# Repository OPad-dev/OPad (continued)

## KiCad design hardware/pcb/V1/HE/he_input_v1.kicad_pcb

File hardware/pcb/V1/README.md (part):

# OPad V1 PCBs

Modular hardware ecosystem joined by one 8-wire JST-SH cable:

| Board | Folder | Size | Status | What it does |
|---|---|---|---|---|
| **Controller carrier** | `Carrier/` | 35.0 × 48.2 mm, C-shaped | Production | Plugs onto the Waveshare ESP32-S3-Touch-LCD-2 headers and brings the module signals to a connector |
| **MX input module** | `MX/` | 52.0 × 24.0 mm | Production | Two Kailh MX mechanical hot-swap sockets under the key plate |
| **Hall Effect input module** | `HE/` | 52.0 × 24.0 mm | **v2 Experimental** | Two magnetic Rapid Trigger Hall sensors (TI DRV5055) under the key plate |

> [!IMPORTANT]
> The **Hall Effect module** requires firmware v2 (Rapid Trigger support), which is not yet available. V1.1 is built and its sensors work on the bench (2026-10-19, [`docs/specs/v2-hall-effect-design.md`](../../docs/specs/v2-hall-effect-design.md) §10b); the firmware's ADC sampling pipeline and Rapid Trigger engine are specified in [`docs/specs/v2-rapid-trigger.md`](../../docs/specs/v2-rapid-trigger.md). v1 firmware recognises an HE module by its ID voltage, shows a warning on the LCD and ignores key input rather than reading the analog sensor outputs as presses.

The input module is **swappable**: both the MX mechanical module and the Hall-effect (rapid trigger) module use the same outline, mounting holes, connector position and pinout, and plug into the same carrier and cable. The module reports which kind it is through an ID voltage on the connector (0.30 V for MX, 1.06 V for Hall Effect).

Production files live in each board's `production/` folder, one subfolder per fab: `jlcpcb/` (Gerbers, BOM, CPL), `pcbway/` (Gerbers with their order marker, BOM, centroid) and `aisler/` (native KiCad board and ODB++ with the parts in them). Renders, PDFs, STEP and the ERC/DRC reports sit next to them.

Status: the MX module and the carrier pass ERC, DRC and schematic parity in KiCad 10.0.6 with zero errors; the carrier has zero warnings, the MX module only "does not match copy in library" warnings, because its footprint and symbol copies were placed before `lib/` was rewritten by `gen_library.py` (same pads and pins; that board is built and working, so `export_production.py` accepts them). The Hall Effect module is generated and checked by its own toolchain (`scripts/he_board.py`, see below), which needs no KiCad install; it reports zero rule violations, its Gerbers verify clean against the netlist, and the generated KiCad files pass ERC and DRC with schematic parity in KiCad 10.0.6 (`scripts/check_he_kicad.py`; only "footprint does not match library" warnings remain, see Toolchain).

---

## Module connector (JST SH 8-pin, same on every input module)

| Pin | Net | Waveshare pin | GPIO | MX V1 use | Hall module use |
|---|---|---|---|---|---|
| 1 | 3V3 | P2-1 | – | pull-ups, ID divider | sensor supply |
| 2 | GND | P2-2 | – | switch common | ground |
| 3 | IN1 | P1-10 | **GPIO10** (ADC1_CH9) | KEY1 (left key) | analog 1 / SPI CS1 |
| 4 | IN2 | P1-9 | **GPIO7** (ADC1_CH6) | KEY2 (right key) | analog 2 / SPI CS2 |
| 5 | ID | P1-8 | GPIO8 (ADC1_CH7) | ID divider = 0.30 V | own ID voltage |
| 6 | IO6 | P1-3 | GPIO6 (ADC1_CH5) | not used | e.g. SPI MISO |
| 7 | IO4 | P1-2 | GPIO4 (ADC1_CH3) | not used | e.g. SPI MOSI |
| 8 | IO2 | P1-1 | GPIO2 (ADC1_CH1) | not used | e.g. SPI SCK |

- All six signals are ADC1 pins. On the ESP32-S3, ADC continuous (DMA) mode only supports ADC1 (see `docs/specs/v2-rapid-trigger.md` §2.2).
- SPI3 can be routed to any of these pins through the GPIO matrix. None of them are strapping pins, USB, UART0, or the touch/IMU I2C.
- The pin order is chosen so both boards route on two layers with no crossings.
- **Firmware:** in the app, set Key 1 = GPIO10 and Key 2 = GPIO7 (both are already in the allowed pin list). The hand-wired defaults (GPIO14 / GPIO9) don't apply to this board.

### Module ID

Each module has its own divider from 3V3 to GND on ID. The carrier has no parts on this line.

| Module | Top resistor | Bottom resistor | ID voltage |
|---|---|---|---|
| MX V1 | 100 kΩ (R3) | 10 kΩ (R4) | 0.30 V |
| **Hall Effect V1** | **100 kΩ (R1)** | **47 kΩ (R2)** | **1.06 V** |
| reserved: Hall SPI | 100 kΩ | 100 kΩ | 1.65 V |

The divider's source impedance is 100k ∥ 47k ≈ 32 kΩ, above the ~10 kΩ the ESP32-S3 ADC likes. ID is read once at start-up, so average a handful of samples instead of trusting a single conversion.

With no module plugged in, GPIO8 floats. The firmware can enable the internal pull-down to read about 0 V in that case.

---

## MX input module (`MX/`)

- **Case coordinates** below are those of `hardware/3d/custom_case/V1/opad_enclosure.scad`: origin at the front-left outer corner, X to the right, Y toward the screen. KiCad uses X = 100 + case X and Y = 100 − case Y, so the top of the KiCad editor is the rear of the case and the layout is not mirrored.
- **Key centres:** case (28.475, 16.5) and (47.525, 16.5), 19.05 mm pitch, the same as the plate cutouts.
- **Outline:** case X 12…64, Y 7…31, 1.5 mm corner radius.
- **Mounting holes:** 2× M2 (2.2 mm NPTH) at case (15.5, 16.5) and (60.5, 16.5), on the key axis and clear of the switch footprints. The PCB must be held there, or it moves when a switch is pulled. Case V1.1 does this without screws: pins in the key deck go through the holes and posts on the bottom plate clamp the PCB against the deck.
- **Height:** the PCB top is **5.0 mm below the top of the plate** (plate 1.5 mm, case z = 10.0). About 3.5 mm of free space is needed under the PCB bottom for the sockets (1.85 mm) and J1 (2.9 mm).
- **Everything is on the bottom side** (sockets, J1, R1–R4, C1), so JLCPCB assembles one side only. The switches go in from the top through the plate.
- **J1** sits at the rear edge, centred on the keys, with the opening facing the screen. The cable leaves toward the controller.
- **Footprint:** `lib/opad.pretty/Kailh_CPG151101S11_MX_Hotswap_Bottom` is the Kailh land pattern (3.05 mm pin holes, 4.0 mm centre, 1.75 mm pegs, 2.55 × 2.5 mm pads), drawn from the socket side and placed flipped. The switch pins point to the rear (standard orientation).

## Hall Effect input module (`HE/`)

Same outline, mounting holes, connector position and pinout as the MX module, so the two are interchangeable on one cable. Instead of switching a pin to ground, each key has a **TI DRV5055A3 ratiometric linear Hall sensor** whose analog output tracks the magnet in the switch stem, which is what rapid trigger needs.

> **V1.0 erratum (fixed in V1.1):** the V1.0 SOT-23 footprint was mirrored, so every assembled sensor sits with **VCC on its IN line and OUT on 3V3**. It powers itself backwards through its protection diode, reads a fixed ~2.9 V and barely reacts to a magnet. The connectivity was right, so neither DRC nor the assembler could catch it. V1.1 swaps pads 1 and 2 (`scripts/gen_library.py`, `scripts/he_board.py`), moves C2/C3 to the pin-1 side so the 3V3 stub and the IN line do not cross, and `he_board.py`'s self-test now checks every SOT-23's pin order against the real package. A V1.0 board works only with each sensor re-soldered upside down (marking towards the board), which mirrors its pin order back.
>
> **V1.1 review (2026-10-10), before ordering:** TI's DBZ pinout (datasheet SBAS640C Figure 4-1 and Table 4-1: 1 = VCC, 2 = OUT, 3 = GND, pin 1 top-left in the top view) was checked against the footprint by hand, against KiCad's flip convention and against the V1.0 measurements; the three agree with the V1.1 pads. Found and fixed in the same pass: the vias grow from 0.6 to **0.7 mm** (0.2 mm annular ring, which Aisler's HASL rules and Eurocircuits' class 6 need; JLCPCB accepted 0.6); the silkscreen square round each sensor was 3.0 mm and crossed the pad tips, it is now 3.6 mm with a pin-1 dot, and `C2`/`C3` moved 0.2 mm away from the sensors to make room; the pour gap went from 0.3 to 0.45 mm and a ground via fills the pocket next to U2, so the Gerbers hold no floating copper slivers (`verify_he_gerbers.py` now checks for islands); the generated schematic had an unescaped quote and did not load in KiCad, so ERC had never actually run on it (it now passes, with PWR_FLAGs and a connector symbol that carries the MP pads). None of these change the netlist.

### Sensor architecture (the part that matters)

This is **Architecture A: bottom-side SMT on solid FR-4.**

- There is **no 4.0 mm stem hole** at the key centres. `SW_MX_Hall_PlateMount` (used for a through-hole stem) is *not* the footprint here; `SW_MX_Hall_PlateMount_SolidCentre` is, and it contributes only the two alignment peg holes.
- U1 and U2 are centred **exactly** on the key centres (16.475, 9.5) and (35.525, 9.5), on the bottom copper, directly under the magnet.
- A **3.0 × 3.0 mm copper keepout on both layers** around each sensor keeps the ground pour out of the magnetic path, so the stem magnet's flux is not damped by eddy currents in the plane. In KiCad these are rule areas with `copperpour not_allowed`; in the Gerbers the pour is genuinely absent there.
### Why there is no centre hole, and what the board is actually compatible with

In a Lekker / Gateron KS-20 class magnetic switch (Gateron's KS-20T drawing DS-02-001-A0, in the [Magnetic Orange datasheet](https://gateron.com/u_file/2312/26/file/GATERONMagneticOrangeSwitch-KS-20TO10B050NW-Y64.pdf), sheet 1):

- **the magnet sits in the stem at the switch centre, N pole towards the PCB.** There is no MX-style centre pole and no 4 mm centre hole;
- **two Ø 1.70 ± 0.05 mm plastic pins, 10.16 mm apart (±5.08 mm), stick out of the bottom and pass straight through the PCB**, protruding about 1 mm out the back. That is why the 1.75 mm peg holes are needed;
- the bottom housing has a pocket ("the hole for setting hall sensor") so Gateron's own reference layout puts a SOT-23 sensor on the **top** of the PCB, between the two pins, with three 0.8 × 0.8 mm pads.

So a top-side sensor is possible with these switches; this board puts it on the bottom instead, like Wooting ([Lekker update #5, part 2](https://wooting.io/post/we-overcame-the-challenges-lekker-update-5-part-22)), because single-side assembly is cheaper and the top of the PCB stays flat against the plate. The price is distance: the magnet reads through the full 1.6 mm of FR-4 plus the package, so the field at the die is a fraction of what Gateron's pocket position sees (numbers under Sensor sensitivity). Peg holes **and** a solid centre **and** a bottom-side sensor is a consistent set; a board that had the peg holes *and* a 4 mm centre hole would be an MX PCB-mount pattern, which is a different switch.

| Switch | Works on this board? |
|---|---|
| Gateron KS-20 / Wooting Lekker, KS-37 / Magnetic Jade, Geon Raw HE and other Lekker-standard magnetic switches | Yes — flush magnet centre, two ±5.08 mm plastic pins |
| Switches sold as "**TMR switches**" | Yes — see below |
| MX mechanical (Cherry, Gateron, Kailh…) | **No.** A real MX switch has a centre pole and metal pins. That is what the `MX/` module is for — same outline, same connector, swap the module |

**On "TMR switches":** TMR (tunnel magnetoresistance) is a *sensor* technology that lives on the keyboard's PCB, not a different kind of switch. A switch marketed as a "TMR switch" is the same magnetic switch — a magnet in an MX-form stem with a flush bottom and two pins — and the industry uses them interchangeably: Gateron Jade, Jade Pro and Lekker V2 all go into Hall boards like the Wooting 60HE and TMR boards like the Womier SK75 alike. This module reads the magnet with a Hall sensor, and the magnet does not know or care what sensor is underneath it, so TMR-branded switches drop straight in.

Two caveats, neither of which is a fit problem:

- **Magnet strength varies by switch model.** TMR sensors are far more sensitive than Hall, so a vendor *can* pair a TMR-targeted switch line with a weaker magnet. If you use such a switch here, A3 is the wrong variant and you want A1 or A2. As Wooting put it, what matters is matching the sensitivity range to the magnet, not chasing sensitivity for its own sake.
- **This board cannot be rebuilt with a TMR sensor as a drop-in.** The common analog TMR parts (MultiDimension TMR2001, TMR2083) are SOT-23-**5**, not the 3-pin SOT-23 used here, so they would need a new footprint and a re-route. Most TMR designs also mount the sensor *off-axis*; U1/U2 here are deliberately on-axis at the key centre, which is the right placement for the DRV5055.

These magnetic switches are deliberately not MX-compatible; vendors say so themselves. The claim this board makes is "every switch in the Lekker standard", not "every keyboard switch ever made". If a magnetic switch turns up with a protruding MX-style centre pole, it will foul the sensor and is out of scope for V1 — I found no current HE switch that does this, since the whole class puts the magnet where that pole would be.

### Sensor sensitivity

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
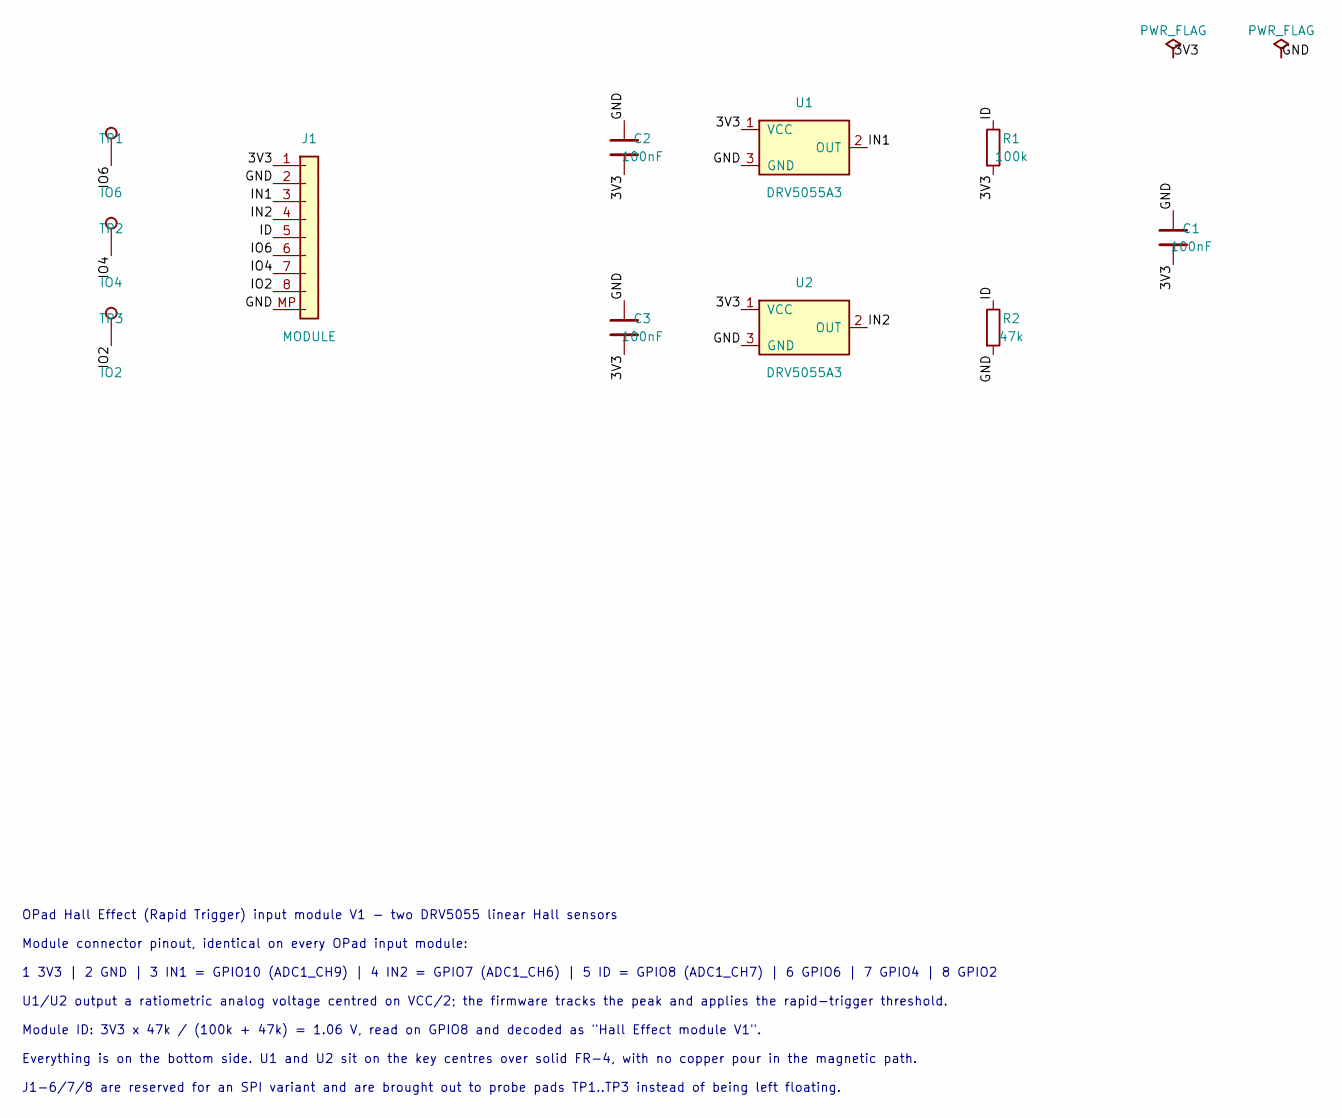
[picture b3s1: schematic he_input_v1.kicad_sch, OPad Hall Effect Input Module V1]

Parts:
C1, C2, C3: 100nF; C_0603_1608Metric; MPN CC0603KRX7R9BB104; LCSC C14663
J1: MODULE; JST_SH_SM08B-SRSS-TB_1x08-1MP_P1.00mm_Horizontal; MPN SM08B-SRSS-TB(LF)(SN); LCSC C160407
R1: 100k; R_0603_1608Metric; MPN 0603WAF1003T5E; LCSC C25803
R2: 47k; R_0603_1608Metric; MPN 0603WAF4702T5E; LCSC C25819
TP1: IO6; TestPoint_Pad_1.0x1.0mm
TP2: IO4; TestPoint_Pad_1.0x1.0mm
TP3: IO2; TestPoint_Pad_1.0x1.0mm
U1, U2: DRV5055A3; SOT-23; MPN DRV5055A3QDBZR; LCSC C266128

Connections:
/3V3: C1.2, C2.2, C3.2, J1.1, R1.2, U1.1 (VCC), U2.1 (VCC)
/GND: C1.1, C2.1, C3.1, J1.2, J1.MP, R2.2, U1.3 (GND), U2.3 (GND)
/ID: J1.5, R1.1, R2.1
/IN1: J1.3, U1.2 (OUT)
/IN2: J1.4, U2.2 (OUT)
/IO2: J1.8, TP3.1
/IO4: J1.7, TP2.1
/IO6: J1.6, TP1.1

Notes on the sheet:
OPad Hall Effect (Rapid Trigger) input module V1 - two DRV5055 linear Hall sensors
Module connector pinout, identical on every OPad input module:
1 3V3 | 2 GND | 3 IN1 = GPIO10 (ADC1_CH9) | 4 IN2 = GPIO7 (ADC1_CH6) | 5 ID = GPIO8 (ADC1_CH7) | 6 GPIO6 | 7 GPIO4 | 8 GPIO2
U1/U2 output a ratiometric analog voltage centred on VCC/2; the firmware tracks the peak and applies the rapid-trigger threshold.
Module ID: 3V3 x 47k / (100k + 47k) = 1.06 V, read on GPIO8 and decoded as "Hall Effect module V1".
Everything is on the bottom side. U1 and U2 sit on the key centres over solid FR-4, with no copper pour in the magnetic path.
J1-6/7/8 are reserved for an SPI variant and are brought out to probe pads TP1..TP3 instead of being left floating.

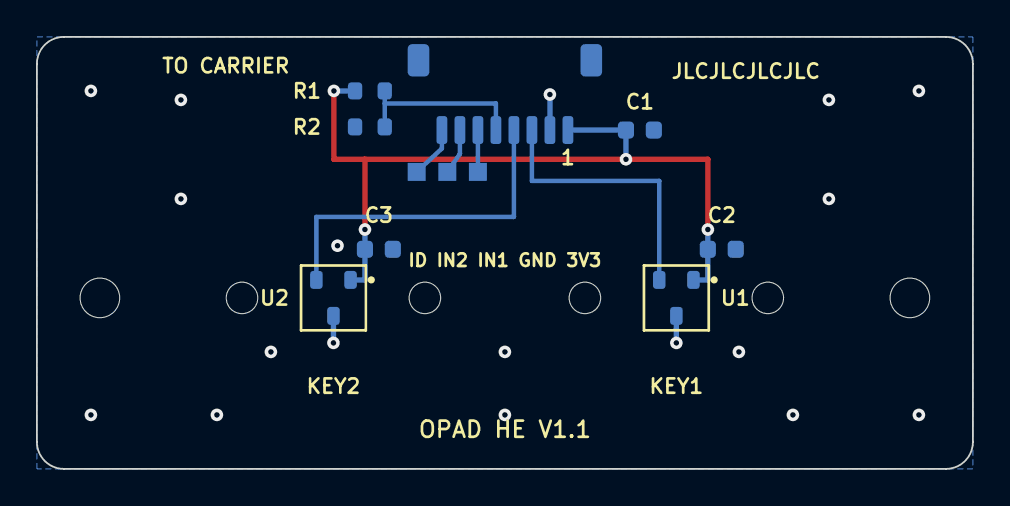
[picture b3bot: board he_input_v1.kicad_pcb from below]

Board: 2 copper layers, 52.0 x 24.0 mm, 15 parts (13 on the bottom side), 8 nets.

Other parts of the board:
H1, H2: MountingHole_2.2mm_M2
SW1: KEY1; SW_MX_Hall_PlateMount_SolidCentre
SW2: KEY2; SW_MX_Hall_PlateMount_SolidCentre

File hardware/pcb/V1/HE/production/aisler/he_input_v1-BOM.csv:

Reference,Quantity,Value,Footprint,MFG,MPN,LCSC,Side,Type
"U1,U2",2,DRV5055A3,SOT-23,Texas Instruments,DRV5055A3QDBZR,C266128,bottom,SMD
"C2,C3,C1",3,100nF,C_0603_1608Metric,YAGEO,CC0603KRX7R9BB104,C14663,bottom,SMD
"J1",1,MODULE,JST_SH_SM08B-SRSS-TB_1x08-1MP_P1.00mm_Horizontal,JST,SM08B-SRSS-TB(LF)(SN),C160407,bottom,SMD
"R1",1,100k,R_0603_1608Metric,UNI-ROYAL,0603WAF1003T5E,C25803,bottom,SMD
"R2",1,47k,R_0603_1608Metric,UNI-ROYAL,0603WAF4702T5E,C25819,bottom,SMD

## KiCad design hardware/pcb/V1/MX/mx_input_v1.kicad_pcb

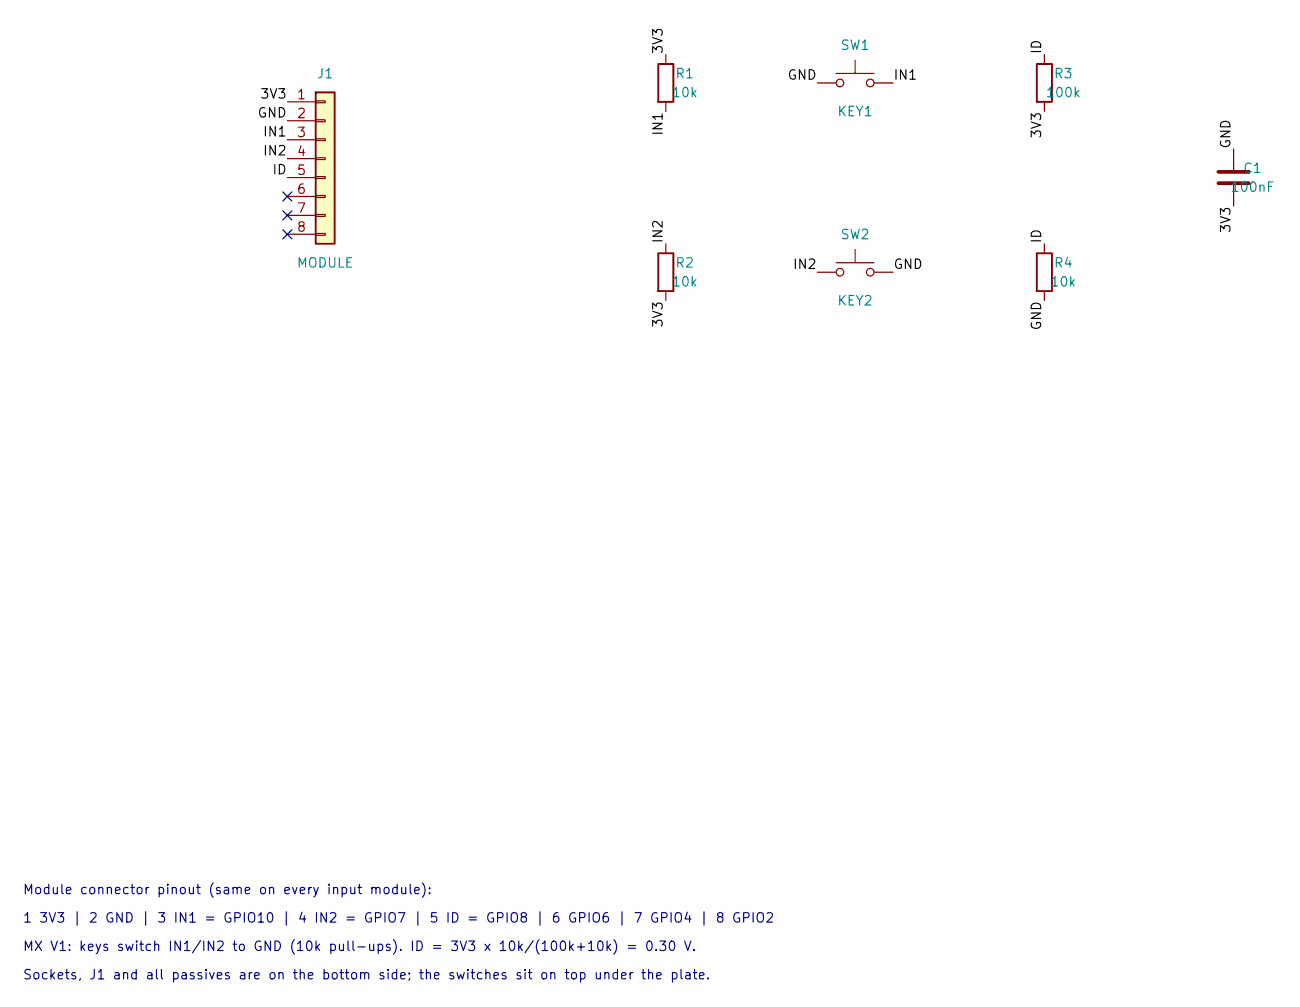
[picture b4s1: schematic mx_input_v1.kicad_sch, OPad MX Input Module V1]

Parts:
C1: 100nF; C_0603_1608Metric; MPN YAGEO CC0603KRX7R9BB104; LCSC C14663
J1: MODULE; JST_SH_SM08B-SRSS-TB_1x08-1MP_P1.00mm_Horizontal; MPN JST SM08B-SRSS-TB(LF)(SN); LCSC C160407
R1, R2, R4: 10k; R_0603_1608Metric; MPN UNI-ROYAL 0603WAF1002T5E; LCSC C25804
R3: 100k; R_0603_1608Metric; MPN UNI-ROYAL 0603WAF1003T5E; LCSC C25803
SW1: KEY1; Kailh_CPG151101S11_MX_Hotswap_Bottom; MPN Kailh CPG151101S11; LCSC C41430893
SW2: KEY2; Kailh_CPG151101S11_MX_Hotswap_Bottom; MPN Kailh CPG151101S11; LCSC C41430893

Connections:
/3V3: C1.2, J1.1, R1.1, R2.2, R3.2
/GND: C1.1, J1.2, R4.2, SW1.1, SW2.2
/ID: J1.5, R3.1, R4.1
/IN1: J1.3, R1.2, SW1.2
/IN2: J1.4, R2.1, SW2.1

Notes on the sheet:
Module connector pinout (same on every input module):
1 3V3 | 2 GND | 3 IN1 = GPIO10 | 4 IN2 = GPIO7 | 5 ID = GPIO8 | 6 GPIO6 | 7 GPIO4 | 8 GPIO2
MX V1: keys switch IN1/IN2 to GND (10k pull-ups). ID = 3V3 x 10k/(100k+10k) = 0.30 V.
Sockets, J1 and all passives are on the bottom side; the switches sit on top under the plate.

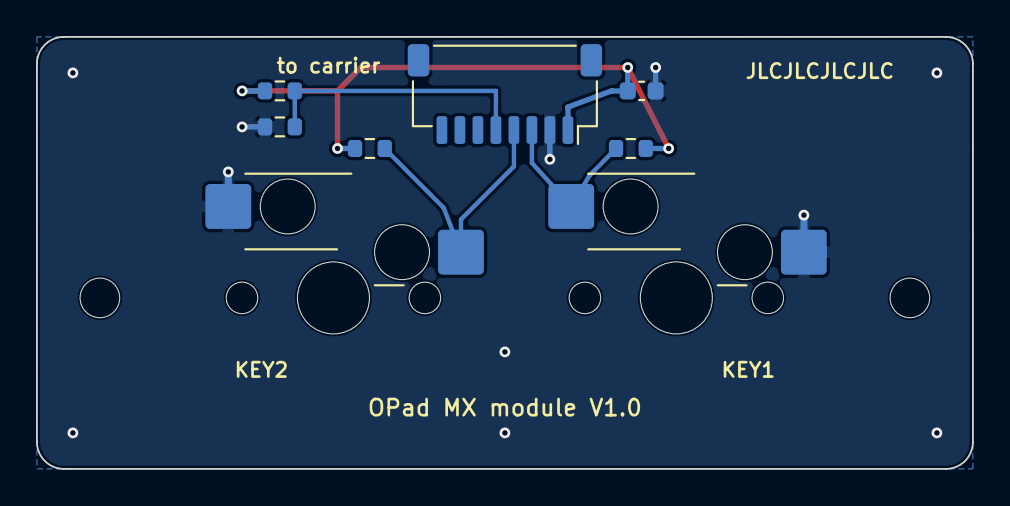
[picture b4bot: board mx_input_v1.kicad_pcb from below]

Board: 2 copper layers, 52.0 x 24.0 mm, 10 parts (8 on the bottom side), 5 nets.

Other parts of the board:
H1, H2: MountingHole_2.2mm_M2

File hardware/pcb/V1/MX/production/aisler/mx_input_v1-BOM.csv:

Reference,Quantity,Value,Footprint,MFG,MPN,LCSC,Side,Type
"R1,R2,R4",3,10k,R_0603_1608Metric,UNI-ROYAL,0603WAF1002T5E,C25804,bottom,SMD
"C1",1,100nF,C_0603_1608Metric,YAGEO,CC0603KRX7R9BB104,C14663,bottom,SMD
"J1",1,MODULE,JST_SH_SM08B-SRSS-TB_1x08-1MP_P1.00mm_Horizontal,JST,SM08B-SRSS-TB(LF)(SN),C160407,bottom,SMD
"R3",1,100k,R_0603_1608Metric,UNI-ROYAL,0603WAF1003T5E,C25803,bottom,SMD
"SW2",1,KEY2,Kailh_CPG151101S11_MX_Hotswap_Bottom,Kailh,CPG151101S11,C41430893,bottom,SMD
"SW1",1,KEY1,Kailh_CPG151101S11_MX_Hotswap_Bottom,Kailh,CPG151101S11,C41430893,bottom,SMD

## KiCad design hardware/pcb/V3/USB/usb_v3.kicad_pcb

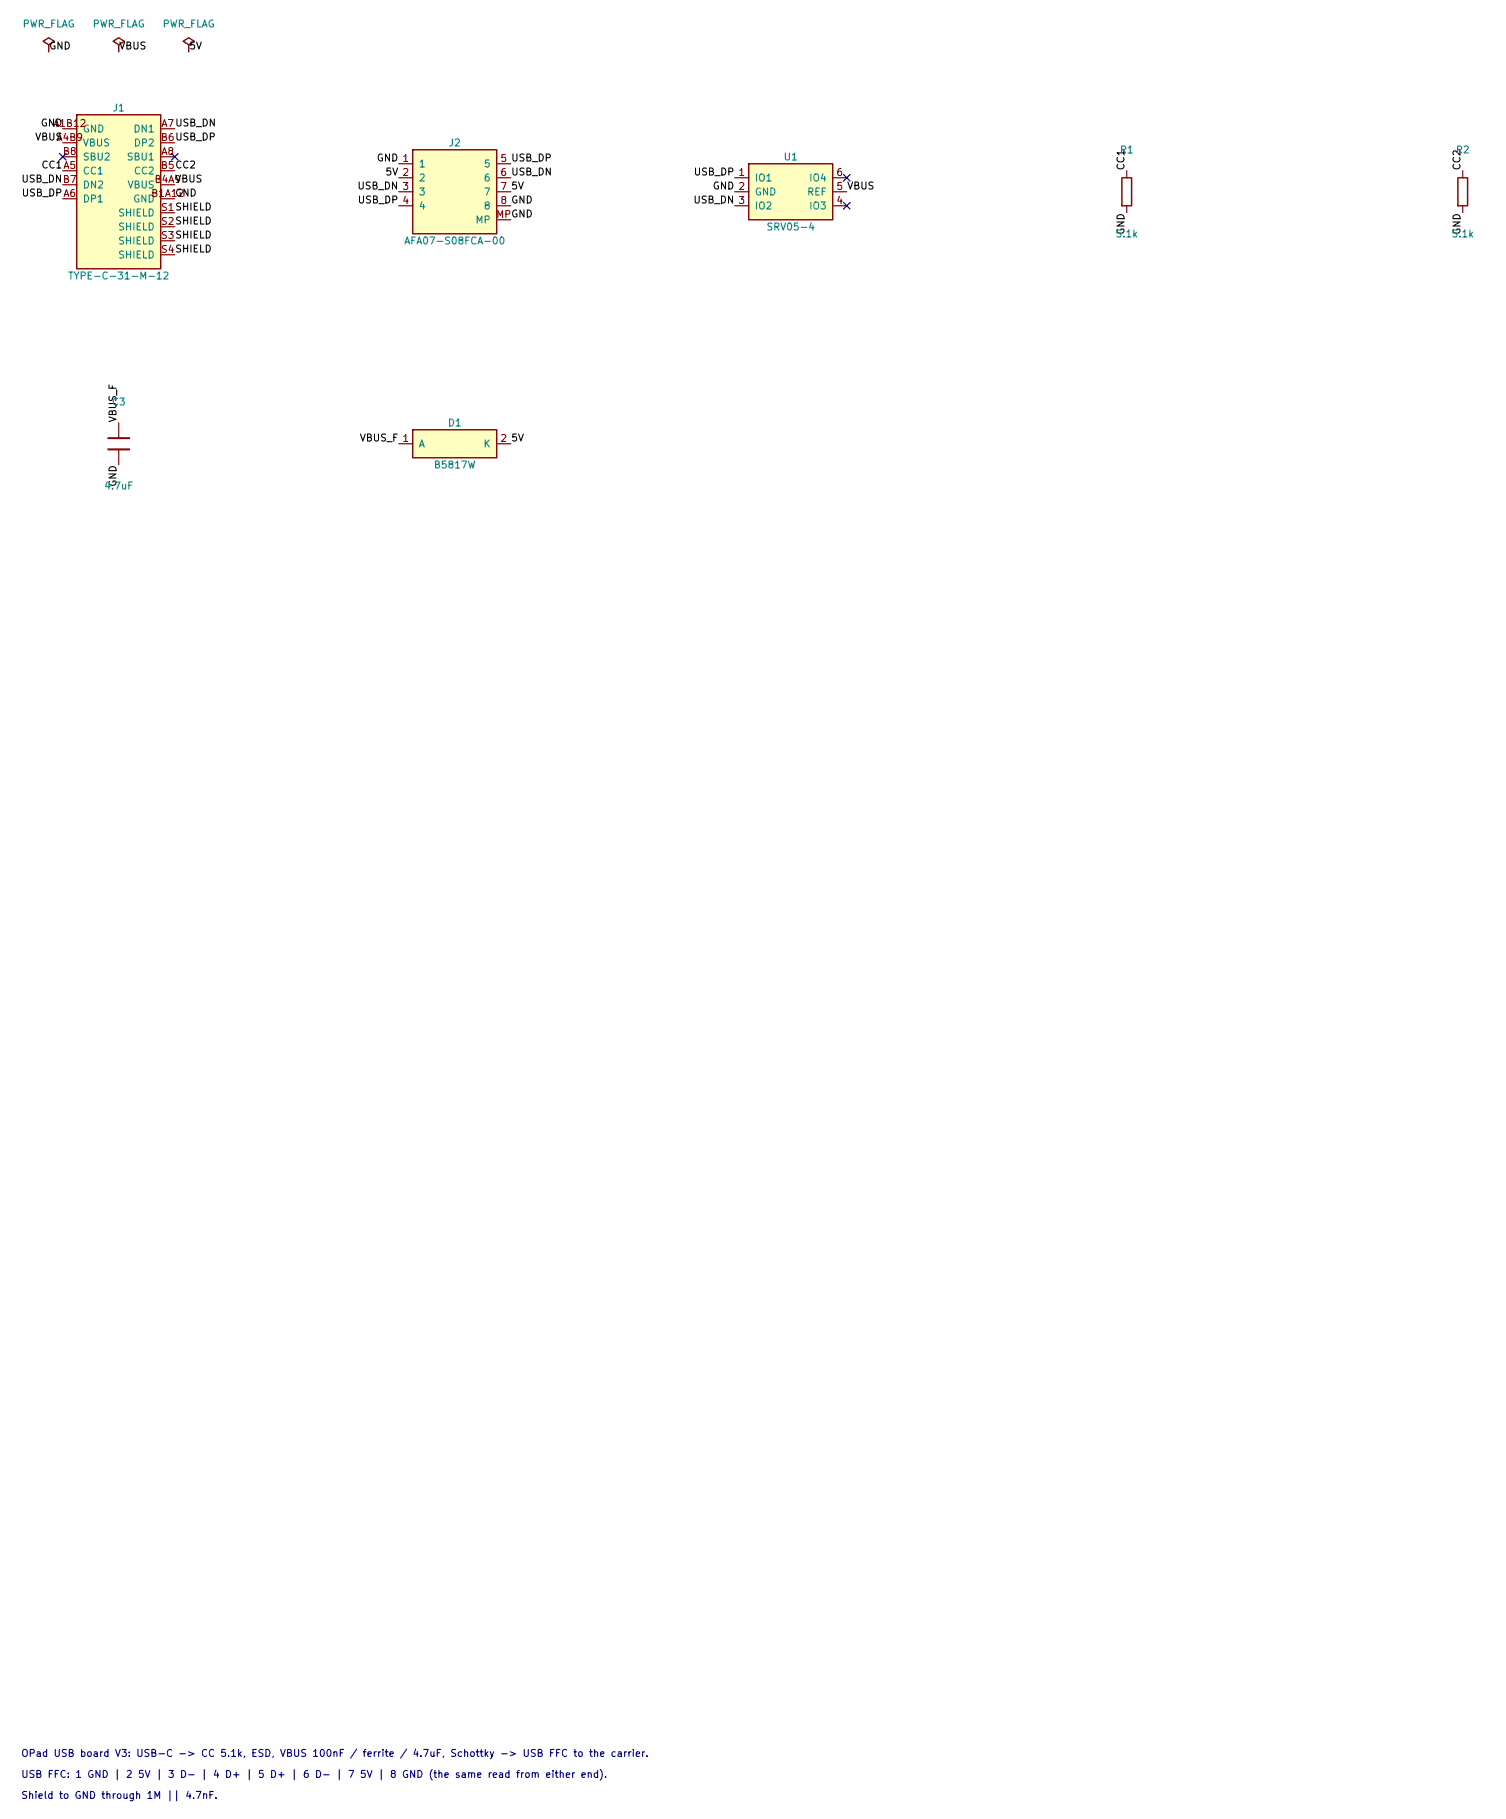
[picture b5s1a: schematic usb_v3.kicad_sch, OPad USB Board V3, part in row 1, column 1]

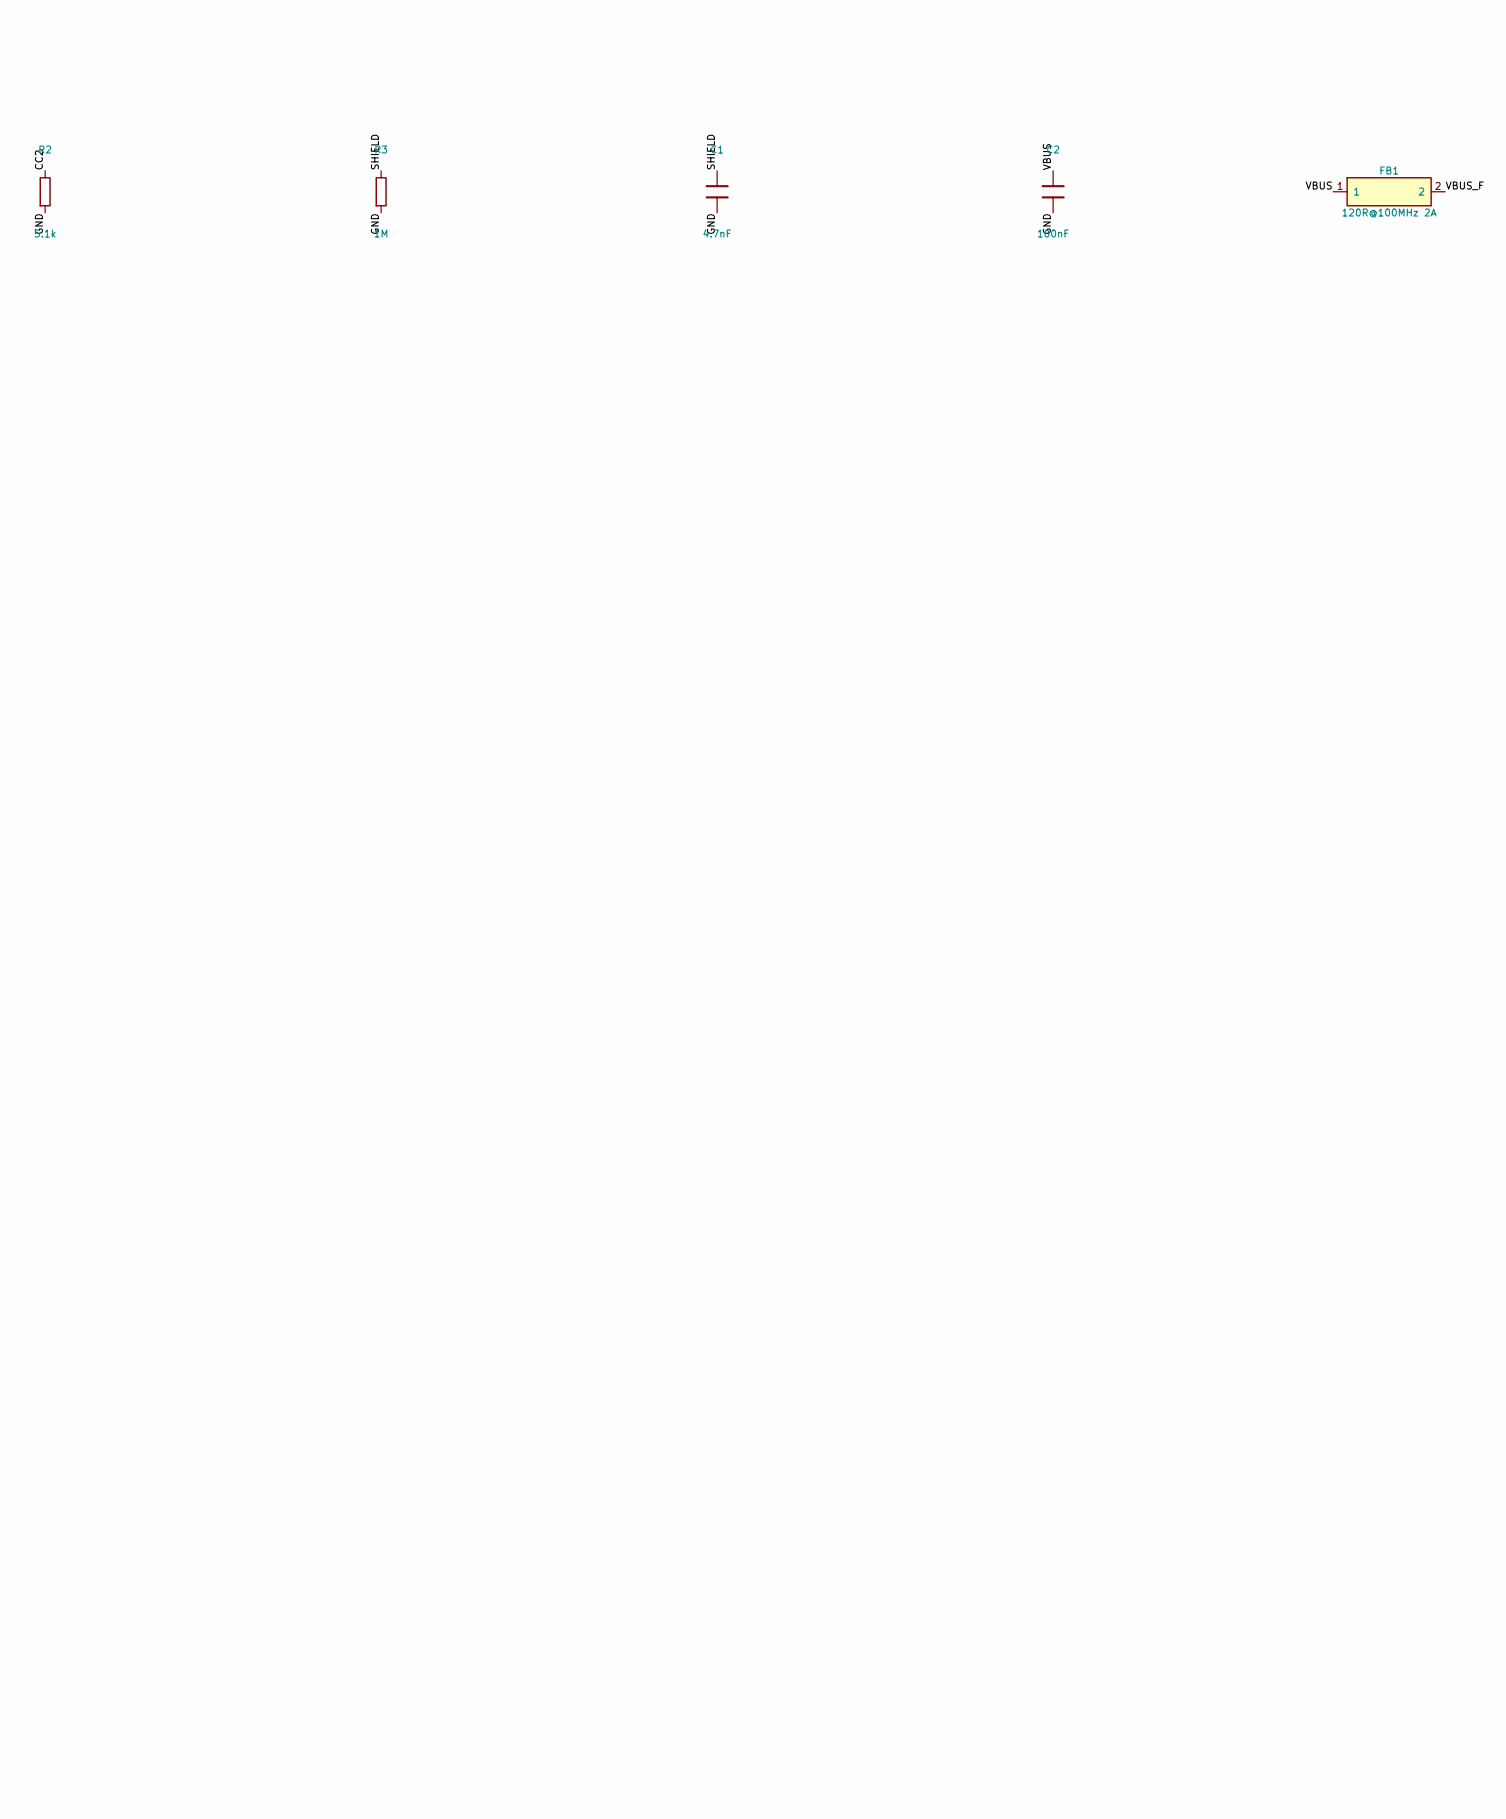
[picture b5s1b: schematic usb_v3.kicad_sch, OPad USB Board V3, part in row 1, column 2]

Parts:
C1: 4.7nF; C_0603_1608Metric; MPN FH 0603B472K500NT; LCSC C53987
C2: 100nF; C_0603_1608Metric; MPN YAGEO CC0603KRX7R9BB104; LCSC C14663
C3: 4.7uF; C_0603_1608Metric; MPN Samsung CL10A475KO8NNNC; LCSC C19666
D1: B5817W; D_SOD-123; MPN R+O B5817W; LCSC C7420328
FB1: 120R@100MHz 2A; L_0603_1608Metric; MPN Murata BLM18PG121SN1D; LCSC C14709
J1: TYPE-C-31-M-12; USB_C_Receptacle_HRO_TYPE-C-31-M-12; MPN Korean Hroparts TYPE-C-31-M-12; LCSC C165948
J2: AFA07-S08FCA-00; FFC_JUSHUO_AFA07-S08FCA_1x08-1MP_P1.0mm_Horizontal; MPN JUSHUO AFA07-S08FCA-00; LCSC C262714
R1, R2: 5.1k; R_0603_1608Metric; MPN UNI-ROYAL 0603WAF5101T5E; LCSC C23186
R3: 1M; R_0603_1608Metric; MPN UNI-ROYAL 0603WAF1004T5E; LCSC C22935
U1: SRV05-4; SOT-23-6; MPN ProTek SRV05-4-P-T7; LCSC C85364

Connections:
/5V: D1.2 (K), J2.2, J2.7
/CC1: J1.A5 (CC1), R1.1
/CC2: J1.B5 (CC2), R2.1
/GND: C1.2, C2.2, C3.2, J1.A1B12 (GND), J1.B1A12 (GND), J2.1, J2.8, J2.MP, R1.2, R2.2, R3.2, U1.2 (GND)
/SHIELD: C1.1, J1.S1 (SHIELD), J1.S2 (SHIELD), J1.S3 (SHIELD), J1.S4 (SHIELD), R3.1
/USB_DN: J1.A7 (DN1), J1.B7 (DN2), J2.3, J2.6, U1.3 (IO2)
/USB_DP: J1.A6 (DP1), J1.B6 (DP2), J2.4, J2.5, U1.1 (IO1)
/VBUS: C2.1, FB1.1, J1.A4B9 (VBUS), J1.B4A9 (VBUS), U1.5 (REF)
/VBUS_F: C3.1, D1.1 (A), FB1.2

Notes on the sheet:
OPad USB board V3: USB-C -> CC 5.1k, ESD, VBUS 100nF / ferrite / 4.7uF, Schottky -> USB FFC to the carrier.
USB FFC: 1 GND | 2 5V | 3 D- | 4 D+ | 5 D+ | 6 D- | 7 5V | 8 GND (the same read from either end).
Shield to GND through 1M || 4.7nF.

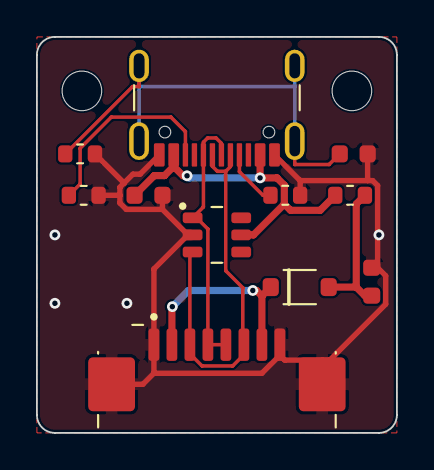
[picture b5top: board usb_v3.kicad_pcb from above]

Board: 2 copper layers, 20.0 x 22.0 mm, 13 parts (0 on the bottom side), 9 nets.

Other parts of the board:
H1, H2: MountingHole_2.2mm_M2

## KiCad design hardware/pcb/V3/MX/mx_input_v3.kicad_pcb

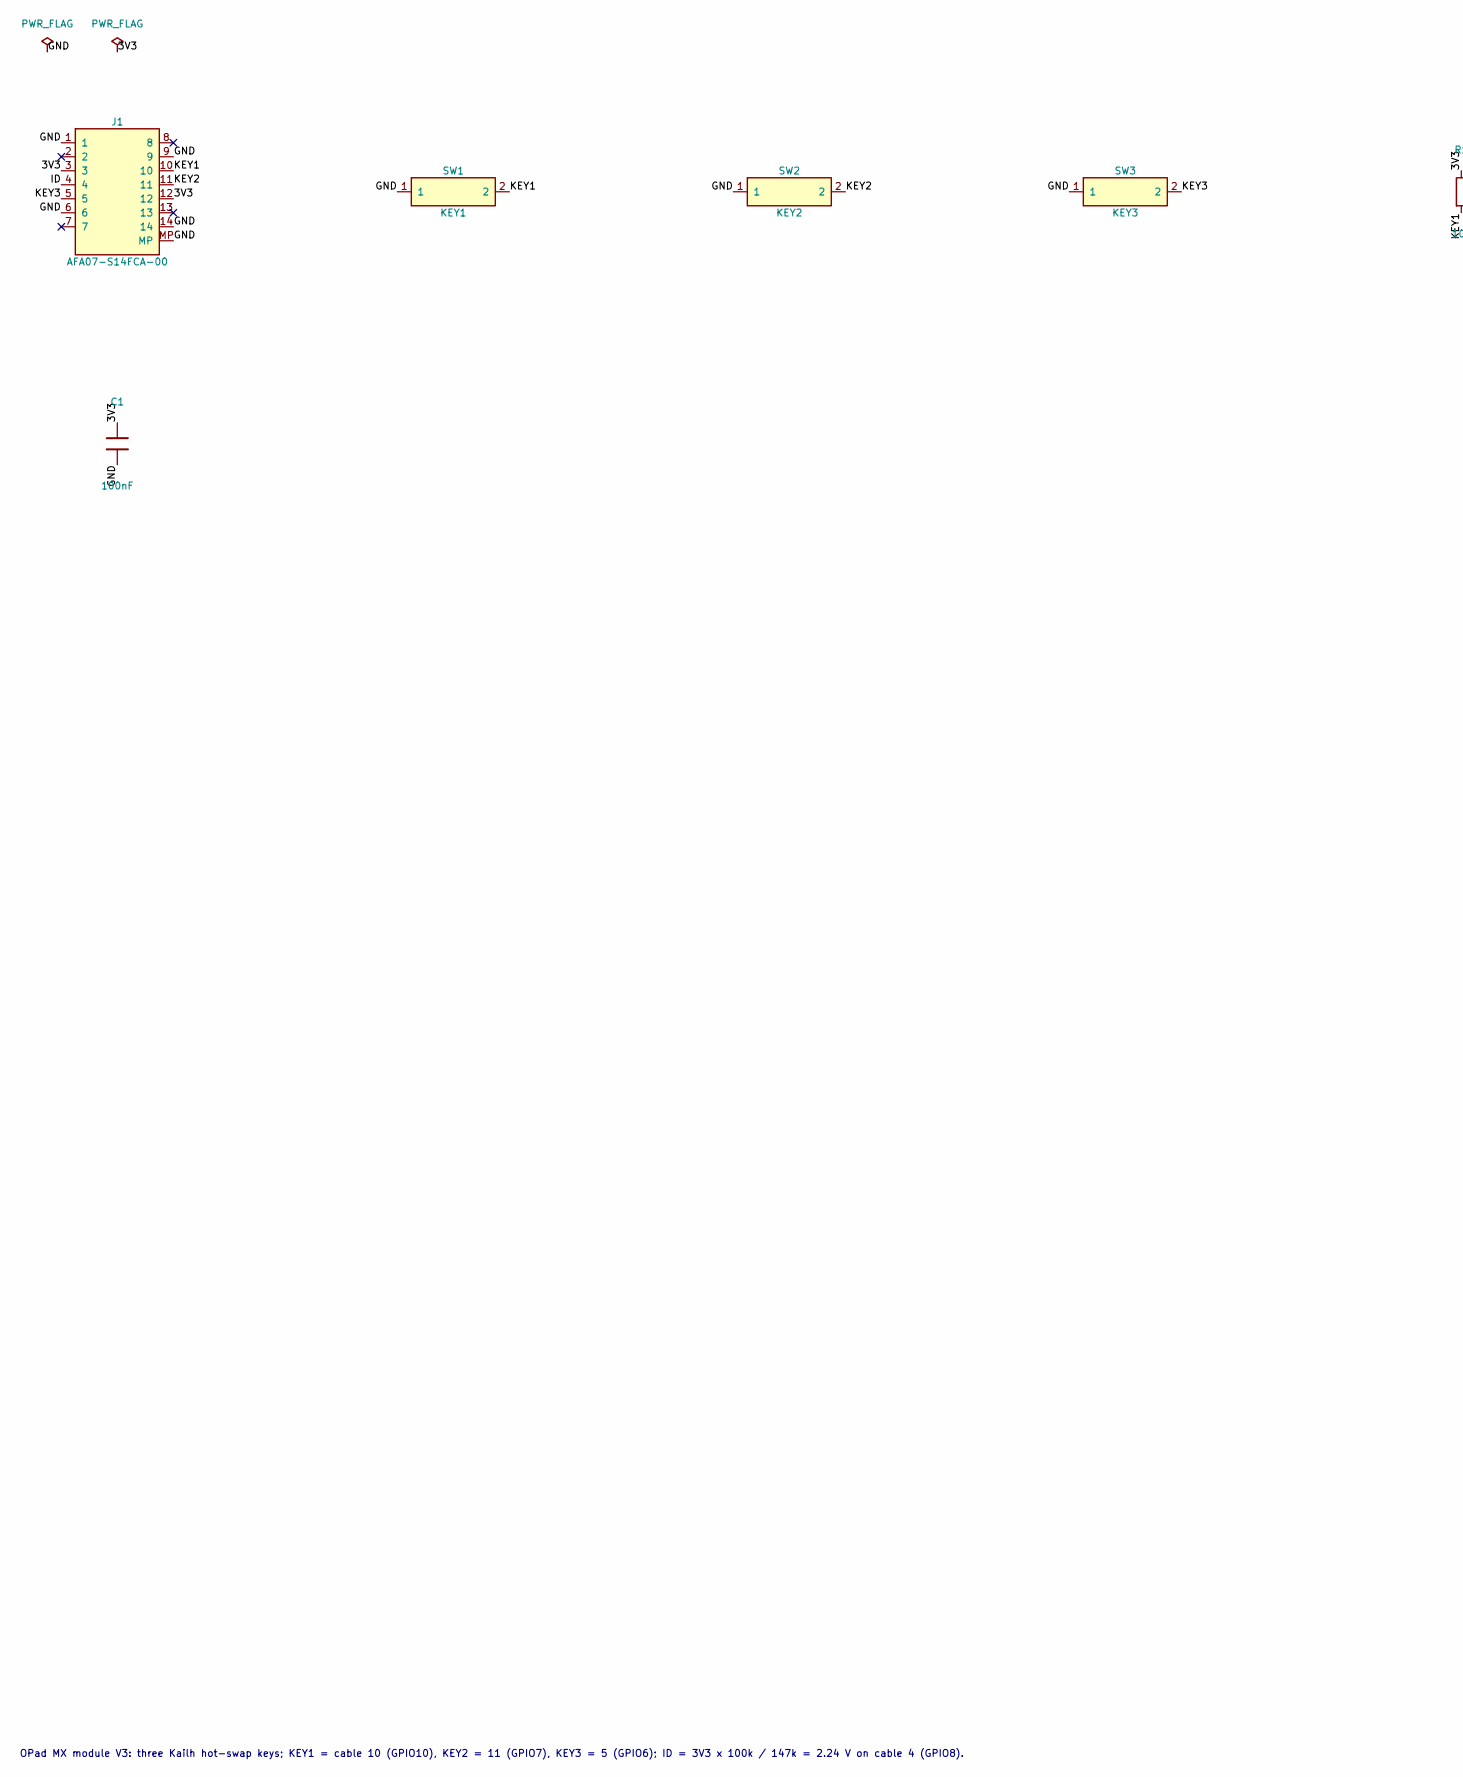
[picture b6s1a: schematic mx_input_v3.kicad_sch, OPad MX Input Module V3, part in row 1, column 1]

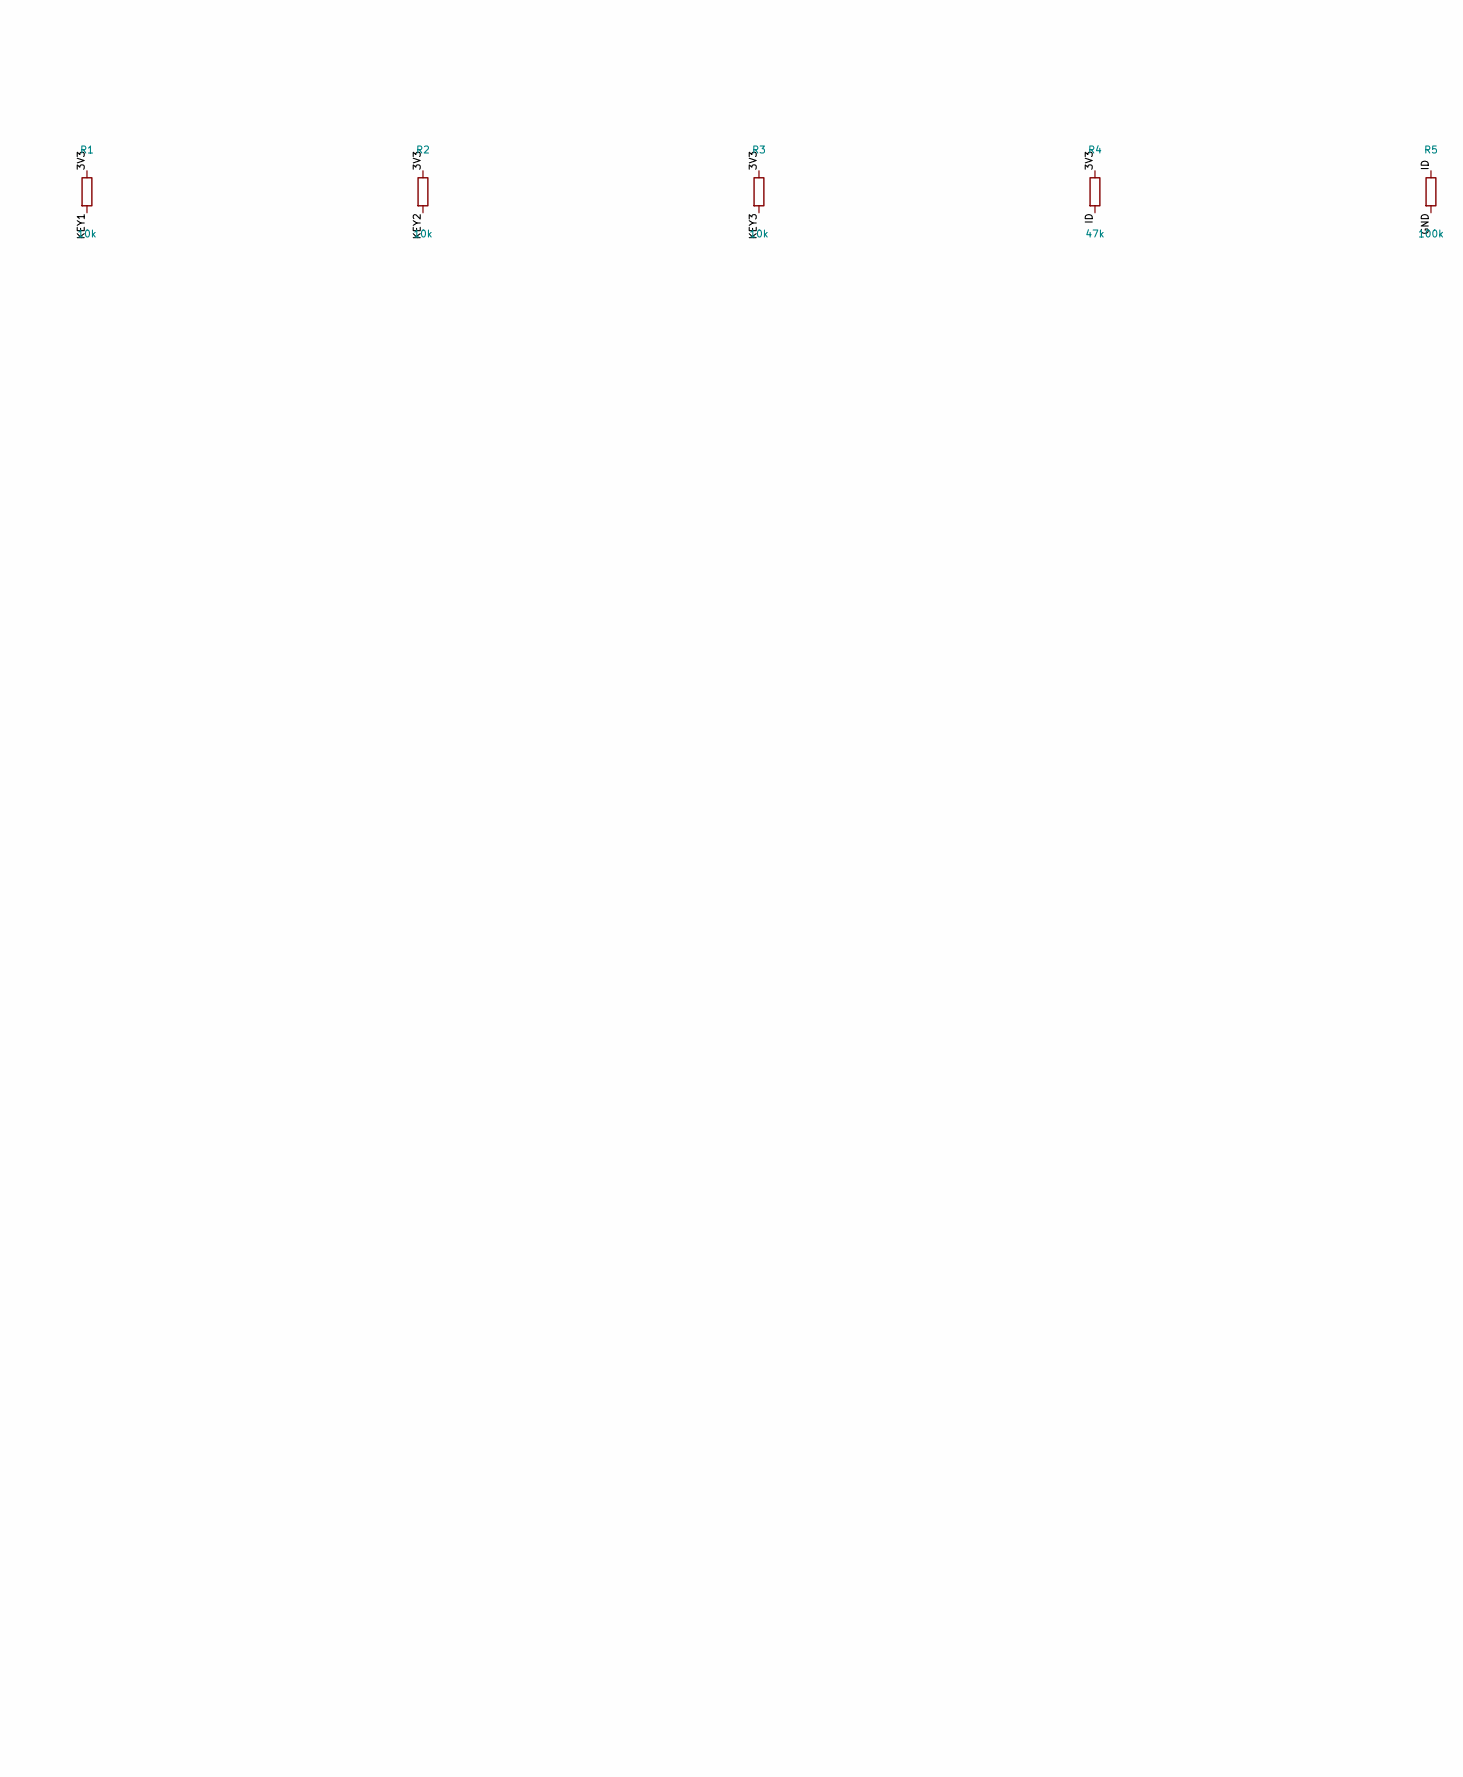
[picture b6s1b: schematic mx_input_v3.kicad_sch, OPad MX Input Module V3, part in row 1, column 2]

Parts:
C1: 100nF; C_0603_1608Metric; MPN YAGEO CC0603KRX7R9BB104; LCSC C14663
J1: AFA07-S14FCA-00; FFC_JUSHUO_AFA07-S14FCA_1x14-1MP_P1.0mm_Horizontal; MPN JUSHUO AFA07-S14FCA-00; LCSC C262720
R1, R2, R3: 10k; R_0603_1608Metric; MPN UNI-ROYAL 0603WAF1002T5E; LCSC C25804
R4: 47k; R_0603_1608Metric; MPN UNI-ROYAL 0603WAF4702T5E; LCSC C25819
R5: 100k; R_0603_1608Metric; MPN UNI-ROYAL 0603WAF1003T5E; LCSC C25803
SW1: KEY1; Kailh_CPG151101S11_MX_Hotswap_Bottom; MPN Kailh CPG151101S11; LCSC C41430893
SW2: KEY2; Kailh_CPG151101S11_MX_Hotswap_Bottom; MPN Kailh CPG151101S11; LCSC C41430893
SW3: KEY3; Kailh_CPG151101S11_MX_Hotswap_Bottom; MPN Kailh CPG151101S11; LCSC C41430893

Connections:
/3V3: C1.1, J1.3, J1.12, R1.1, R2.1, R3.1, R4.1
/GND: C1.2, J1.1, J1.6, J1.9, J1.14, J1.MP, R5.2, SW1.1, SW2.1, SW3.1
/ID: J1.4, R4.2, R5.1
/KEY1: J1.10, R1.2, SW1.2
/KEY2: J1.11, R2.2, SW2.2
/KEY3: J1.5, R3.2, SW3.2

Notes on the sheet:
OPad MX module V3: three Kailh hot-swap keys; KEY1 = cable 10 (GPIO10), KEY2 = 11 (GPIO7), KEY3 = 5 (GPIO6); ID = 3V3 x 100k / 147k = 2.24 V on cable 4 (GPIO8).

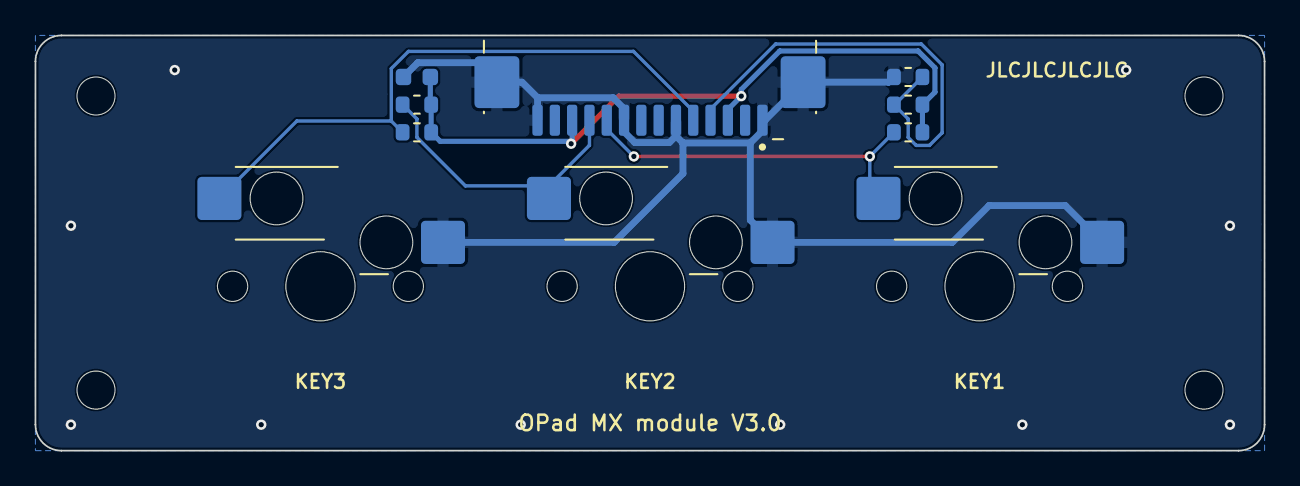
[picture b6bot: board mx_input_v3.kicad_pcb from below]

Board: 2 copper layers, 71.0 x 24.0 mm, 14 parts (10 on the bottom side), 6 nets.

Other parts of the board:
H1, H2, H3, H4: MountingHole_2.2mm_M2
